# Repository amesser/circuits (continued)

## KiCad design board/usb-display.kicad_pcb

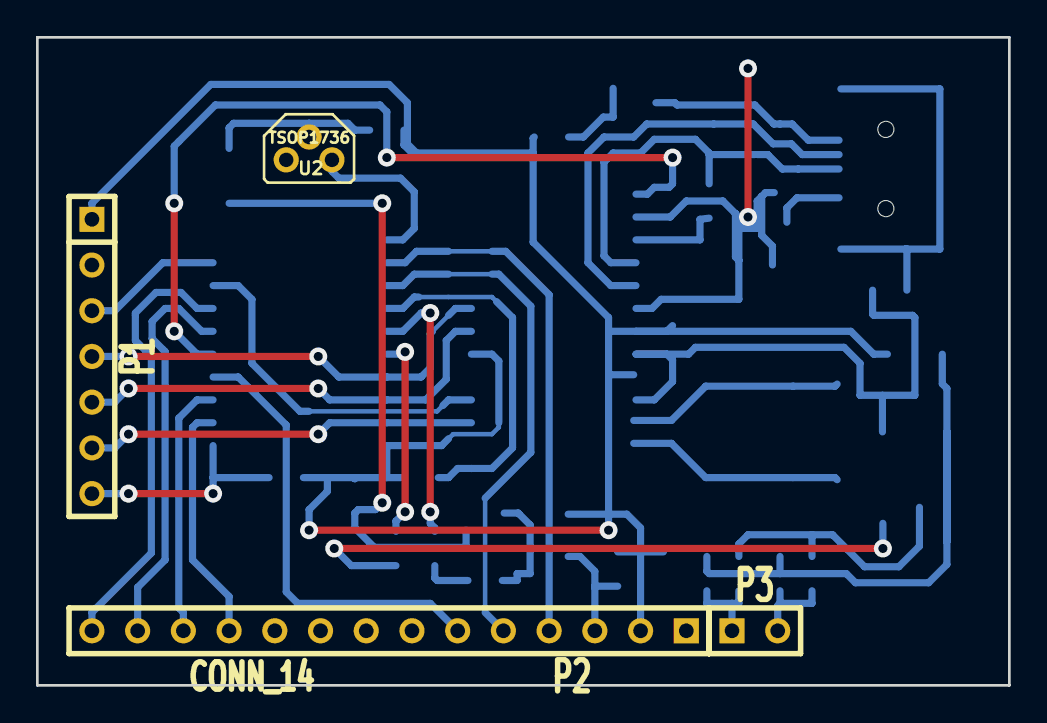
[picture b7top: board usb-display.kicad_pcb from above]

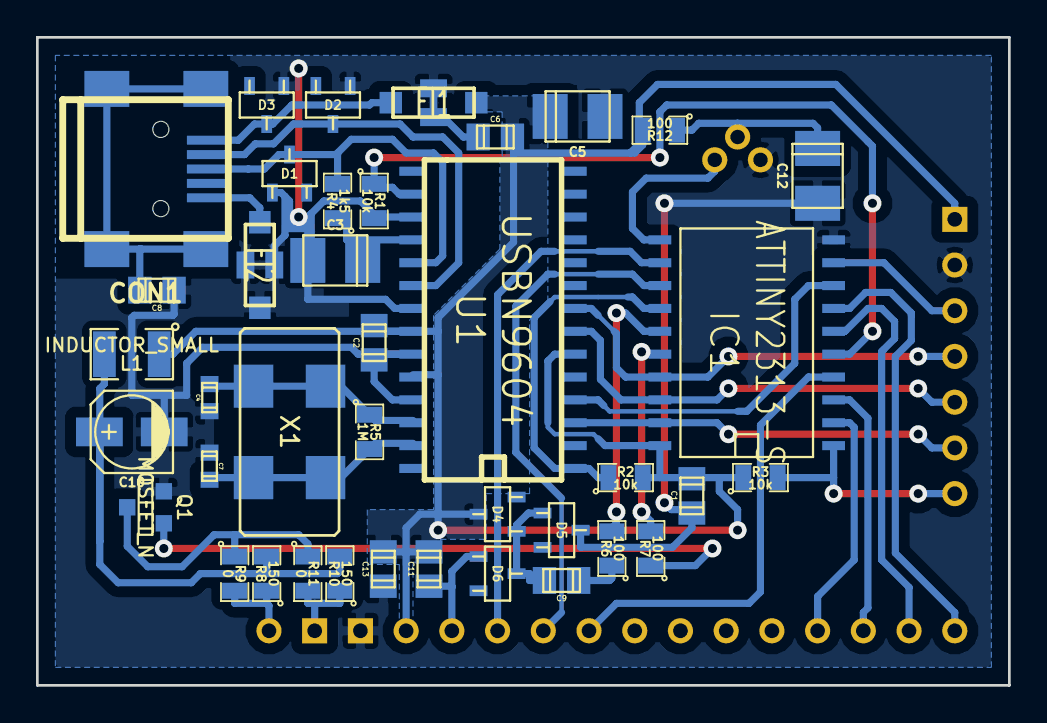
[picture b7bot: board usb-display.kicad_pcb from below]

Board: 2 copper layers, 54.0 x 36.0 mm, 43 parts (39 on the bottom side), 37 nets.

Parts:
C1, C2, C6, C8, C9, C11, C13: 100n; c_0805
C3: 1µ Tantal; c_tant_B
C4, C7: 15p; c_0603
C5: 10µ; c_tant_B
C10: 100µ; c_elec_4x4.5
C12: 4µ7; c_tant_B
CON1: USB-MINI-B; USB_MINI_B
D1, D2, D3: ZENER; sot23
D4, D5, D6: DIODESCH; sot23
FI1, FI2: EMI_FILTER2; emi_smd_1806
IC1: ATTINY2313-S; SO20L
L1: INDUCTOR_SMALL; SM1210
P1: CONN_7; SIL-7
P2: CONN_14; SIL-14
P3: CONN_2; SIL-2
Q1: MOSFET_N; SOT23GDS
R1, R2, R3: 10k; SM0805
R4: 1k5; SM0805
R5: 1M; SM0805
R6, R7, R12: 100; SM0805
R8, R10: 150; SM0805
R9, R11: 0; SM0805
U1: USBN9604; SO28
U2: TSOP1736; TO92PN
X1: 24MHz; crystal_c1

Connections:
+5V: C1.1, C2.1, C5.1, C6.1, C11.1, C13.1, D4.2, FI1.3, IC1.20, L1.1, P1.1, P2.2, R2.2, R3.1, R12.2, U1.6, U1.22, U1.24
/BACKLIGHT_PWM: IC1.16, R7.2
/CONTRAST_PWM: IC1.15, R6.2
/DISPLAY_D0: IC1.2, P2.11
/DISPLAY_D1: IC1.3, P2.12
/DISPLAY_D2: IC1.6, P2.13
/DISPLAY_D3: IC1.7, P2.14
/DISPLAY_ENABLE: IC1.4, P2.6
/DISPLAY_RS: IC1.12, P2.4
/DISPLAY_RW: IC1.13, P2.5
/EXT_CS: IC1.9, P1.3
/IR: IC1.11, U2.3
/RESET: IC1.1, P1.7, R3.2
/USB_CS: IC1.14, R2.1, U1.1
/USB_INTR: IC1.8, U1.4
/USB_RESET: IC1.5, R1.1, U1.16
/USB_SCK: IC1.19, P1.6, U1.3
/USB_SI: IC1.18, P1.5, U1.7
/USB_SO: IC1.17, P1.4, U1.8
GND: C1.2, C2.2, C3.2, C4.2, C5.2, C6.2, C7.2, C8.2, C10.2, C12.2, C13.2, D1.1, D2.1, D3.1, D5.2, FI1.2, FI2.2, FI2.3, IC1.10, P1.2, P2.1, Q1.S, R1.2, U1.17, U1.21, U1.23, U1.25, U2.1
unnamed: P3.1, R10.1, R11.2
unnamed: C11.2, D6.1, P2.3
unnamed: C9.1, D4.1, D5.1, D6.2
unnamed: C10.1, L1.2, R8.2, R10.2
unnamed: Q1.G, R7.1
unnamed: Q1.D, R9.1, R11.1
unnamed: C8.1, CON1.6, CON1.7, CON1.8, CON1.9
unnamed: CON1.5, FI2.1
unnamed: C3.1, R4.1, U1.18
unnamed: CON1.1, D3.2, FI1.1
unnamed: CON1.3, D1.2, R4.2, U1.19
unnamed: CON1.2, D2.2, U1.20
unnamed: P3.2, R8.1, R9.2
unnamed: C12.1, R12.1, U2.2
unnamed: C7.1, R5.2, U1.27, X1.2
unnamed: C9.2, R6.1
unnamed: C4.1, R5.1, U1.26, X1.1
